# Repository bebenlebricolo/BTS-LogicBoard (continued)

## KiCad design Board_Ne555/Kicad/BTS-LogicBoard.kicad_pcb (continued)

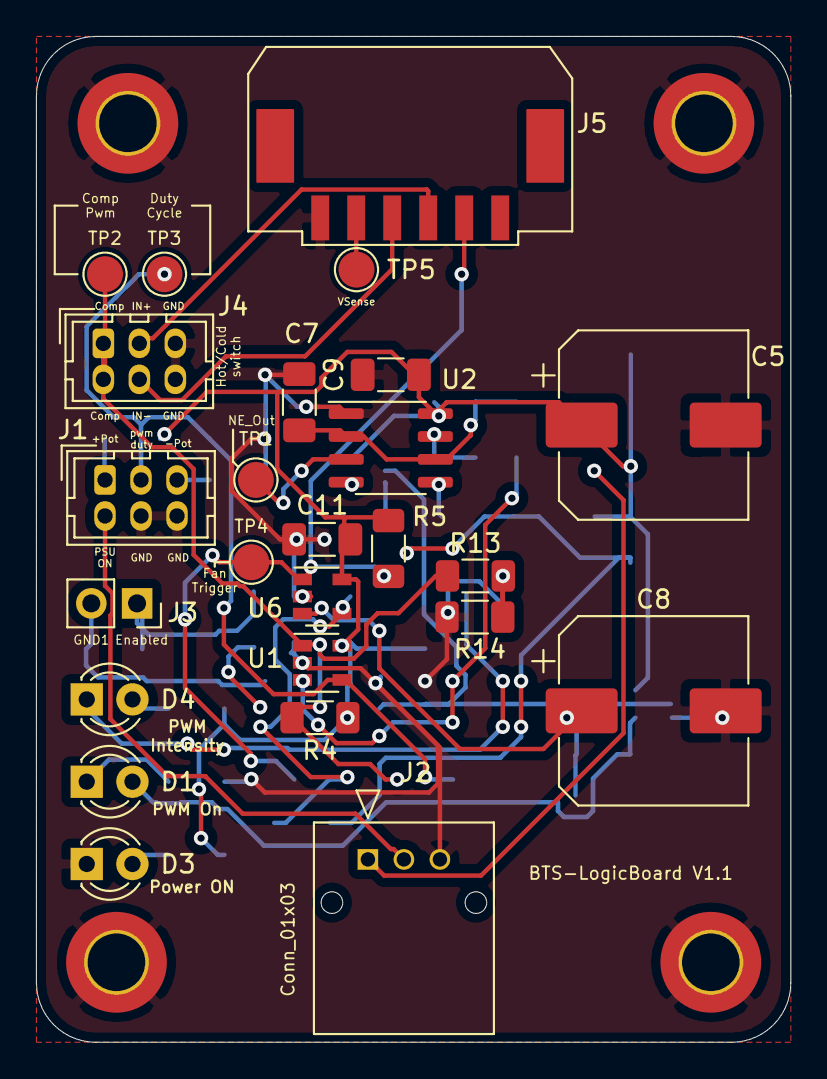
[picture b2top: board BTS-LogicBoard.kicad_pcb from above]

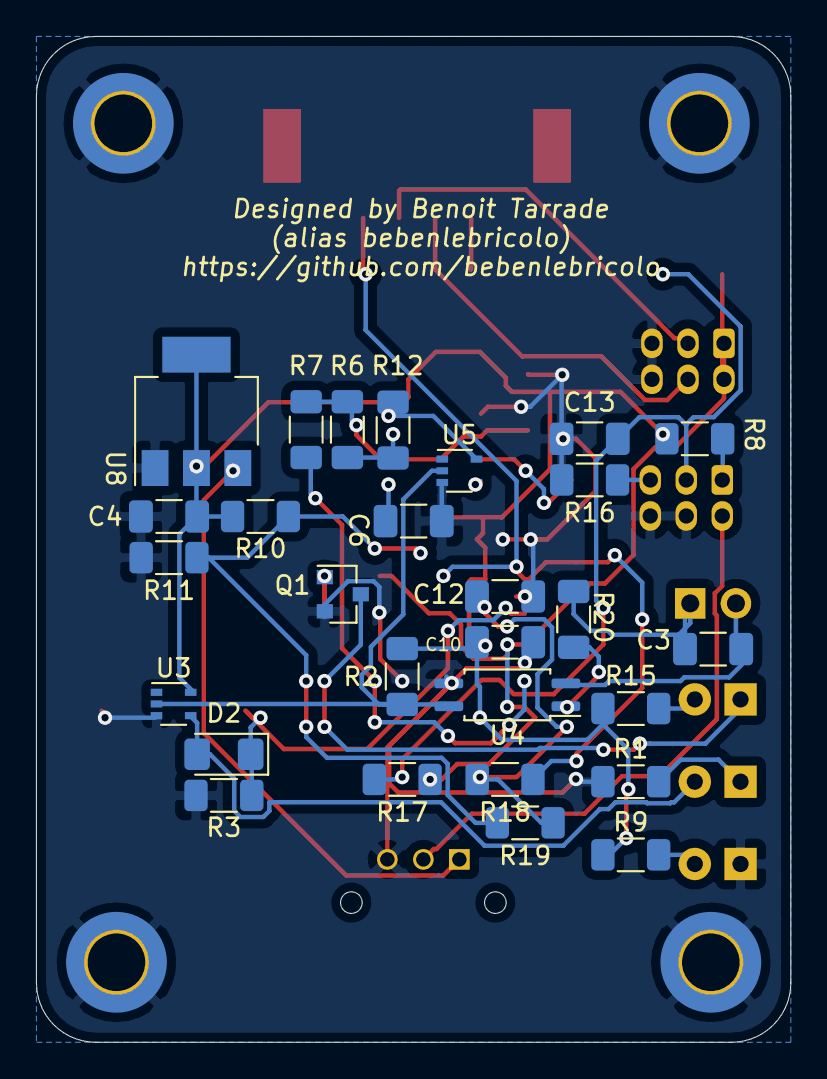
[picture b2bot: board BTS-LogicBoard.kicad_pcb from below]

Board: 2 copper layers, 41.9 x 55.9 mm, 57 parts (28 on the bottom side), 31 nets.

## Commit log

2021-09-10 Copied Simulations from BTS-MainBoard-Power
2021-09-10 Created Kicad project + gitignore file
2021-09-10 Finished schematic
2021-09-10 Removed netlist for simulations
2021-09-10 Started to assign footprints
2021-09-11 Added fan triggering simulation
2021-09-11 Started footprint placement on board
2021-09-11 Started routing
2021-09-12 Added NE555 enable override by HIP_DISABLE signal
2021-09-12 Finalized board V1 and exported Gerber files
2021-09-12 Fan trigger now uses 5V instead of 12v to prevent blowing up fans mosfets
2021-09-14 Updated .gitignore
2021-09-14 Updated Gerbers
2021-09-14 Updated silkscreen and Gerbers
2021-09-15 Created BOM
2021-10-04 Updated Gerbers
    igned-off-by: bebenlebricolo <benoittarrade@hotmail.fr>
2021-10-04 Updated BOM
2021-10-04 Swapped 12Vcc on NE555 outputs and remapped comparators
2021-10-04 Reworking NCS comparators output interface + led logics
2021-10-04 Fixed unatural DPDT switch mapping
2021-10-04 Updated board with optocoupler
2021-10-04 Modified a little bit fan triggering circuit
2021-10-05 Updated schematic with proper inverter (not gates) logic layout
2021-10-09 Added symbols and footprints for TE EP 01x04 connector
2021-10-09 Updated schematic with LEDS and new NE555/TS555 PWM generation circuit
2021-10-09 Added footprints
2021-10-09 Restarted layout
2021-10-09 Finalized layout for Version 1.1 (need to work on silkscreen now)
2021-10-10 Finalized board layout with silkscreen
2021-10-14 Tried to understand why comparator output is so ringy
2021-10-14 Added comparator with pot and hysteresis simulation
2021-10-15 Added hysteresis resistor to comparators and reexported gerbers
2021-10-15 Forgot to add another hysteresis resistor : done
2021-10-29 Added prototype v1.1 bom
2021-10-29 Annotated schematic
2021-11-09 Added some Simulations to test discrete h bridge driver implementations
2021-11-09 Added Notes for board revision v0.1.0
2021-11-09 Updated notes for both board revisions
2021-11-10 Renamed Versions folder into Notes and added some more notes
2021-11-10 Updated notes and readme
2022-01-03 Modified global readme
2022-01-03 Moved Ne555 based board design elements to the right folder
2022-01-03 Added pin compatibilities calc file to compare two avr mcus
2022-01-03 Started LogicBoard desing based on avr mcus
2022-01-03 Added the Mechanical user interface hierarchical sheet and started schematics
2022-01-03 Designed basic layout for the mechanical user interface
2022-01-03 Added several other schematic sheets
2022-01-04 Added several external connections and reworked leds and output signals
2022-01-04 Updated pin configurations in PinCompatibilities.ods
2022-01-04 Fixed misorganised pins and updated pin mapping table
2022-01-05 Started routing all traces
2022-01-05 Removed all microvias (unsupported by JLCPCB)
2022-01-06 Rerouted parts of the board and improved zones
2022-01-06 Updated VCC and 3.3V zones
2022-01-06 Finalised routing
2022-01-06 Cleaned last remaining track bits
2022-01-06 Same using the automatic cleanup tracks and via tool
2022-01-06 Fixed silkscreen and added PWM signal test points
2022-01-07 Tweaked top silkscreen to embed useful information
2022-01-07 Finalised routing and finalised silkscreen
2022-01-07 Updated documentation with screenshots
2022-01-07 Backed up modifications on schematic as well
2022-01-14 Replaced TLV1117-3.3 by NCP630SN330 and polished a bit zoning
2022-01-15 Removed unused pads from vias in order to improve polygons
2022-01-19 Added BTS logos and updated silkscreen
2022-01-20 Generated Gerbers and BOM files
2022-01-20 Moved Gerbers around and updated 3d model of optocoupler
2022-01-24 Updated ferrite bead footprint
2022-02-09 Added some comments on V0.3.0
2022-02-23 Updated board with external clock for both mcus + thermal reliefs update
